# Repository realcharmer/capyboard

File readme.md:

# Capyboard

This repository contains the KiCad source files for the Capyboard development board and its individual modules.

See more at <https://docs.capyboard.dev/modules/mainboard/>.

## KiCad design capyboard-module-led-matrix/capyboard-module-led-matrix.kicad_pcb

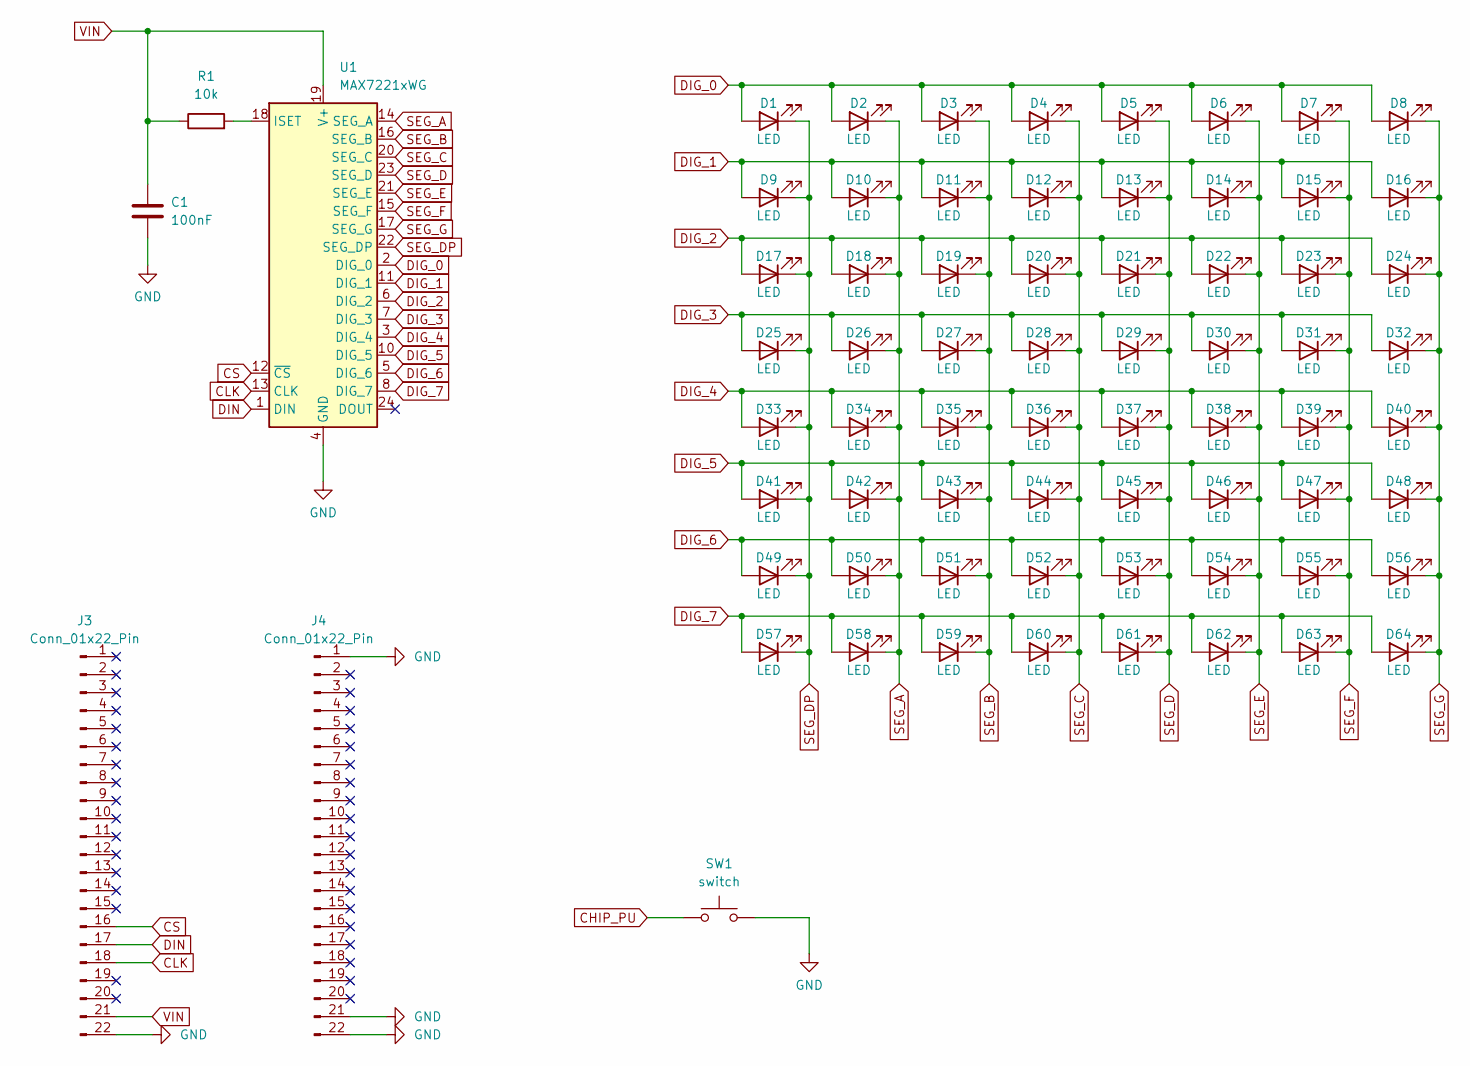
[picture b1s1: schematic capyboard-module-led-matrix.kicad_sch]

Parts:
C1: 100nF; C_0805_2012Metric
D1, D2, D3, D4, D5, D6, D7, D8, D9, D10, D11, D12, D13, D14, D15, D16, D17, D18, D19, D20, D21, D22, D23, D24, D25, D26, D27, D28, D29, D30, D31, D32, D33, D34, D35, D36, D37, D38, D39, D40, D41, D42, D43, D44, D45, D46, D47, D48, D49, D50, D51, D52, D53, D54, D55, D56, D57, D58, D59, D60, D61, D62, D63, D64: LED; LED_0805_2012Metric
J3: Conn_01x22_Pin; PinSocket_1x22_P2.54mm_Vertical_SMD_Pin1Left
J4: Conn_01x22_Pin; PinSocket_1x22_P2.54mm_Vertical_SMD_Pin1Right
R1: 10k; R_0805_2012Metric
SW1: switch; SW_Push_1P1T_NO_CK_KMR2
U1: MAX7221xWG; SOIC-24W_7.5x15.4mm_P1.27mm

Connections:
CHIP_PU: J4.3, SW1.1
CLK: J3.18, U1.13 (CLK)
CS: J3.16, U1.12 (~CS)
DIG_0: D1.2 (A), D2.2 (A), D3.2 (A), D4.2 (A), D5.2 (A), D6.2 (A), D7.2 (A), D8.2 (A), U1.2 (DIG_0)
DIG_1: D9.2 (A), D10.2 (A), D11.2 (A), D12.2 (A), D13.2 (A), D14.2 (A), D15.2 (A), D16.2 (A), U1.11 (DIG_1)
DIG_2: D17.2 (A), D18.2 (A), D19.2 (A), D20.2 (A), D21.2 (A), D22.2 (A), D23.2 (A), D24.2 (A), U1.6 (DIG_2)
DIG_3: D25.2 (A), D26.2 (A), D27.2 (A), D28.2 (A), D29.2 (A), D30.2 (A), D31.2 (A), D32.2 (A), U1.7 (DIG_3)
DIG_4: D33.2 (A), D34.2 (A), D35.2 (A), D36.2 (A), D37.2 (A), D38.2 (A), D39.2 (A), D40.2 (A), U1.3 (DIG_4)
DIG_5: D41.2 (A), D42.2 (A), D43.2 (A), D44.2 (A), D45.2 (A), D46.2 (A), D47.2 (A), D48.2 (A), U1.10 (DIG_5)
DIG_6: D49.2 (A), D50.2 (A), D51.2 (A), D52.2 (A), D53.2 (A), D54.2 (A), D55.2 (A), D56.2 (A), U1.5 (DIG_6)
DIG_7: D57.2 (A), D58.2 (A), D59.2 (A), D60.2 (A), D61.2 (A), D62.2 (A), D63.2 (A), D64.2 (A), U1.8 (DIG_7)
DIN: J3.17, U1.1 (DIN)
unnamed: R1.2, U1.18 (ISET)
SEG_A: D2.1 (K), D10.1 (K), D18.1 (K), D26.1 (K), D34.1 (K), D42.1 (K), D50.1 (K), D58.1 (K), U1.14 (SEG_A)
SEG_B: D3.1 (K), D11.1 (K), D19.1 (K), D27.1 (K), D35.1 (K), D43.1 (K), D51.1 (K), D59.1 (K), U1.16 (SEG_B)
SEG_C: D4.1 (K), D12.1 (K), D20.1 (K), D28.1 (K), D36.1 (K), D44.1 (K), D52.1 (K), D60.1 (K), U1.20 (SEG_C)
SEG_D: D5.1 (K), D13.1 (K), D21.1 (K), D29.1 (K), D37.1 (K), D45.1 (K), D53.1 (K), D61.1 (K), U1.23 (SEG_D)
SEG_DP: D1.1 (K), D9.1 (K), D17.1 (K), D25.1 (K), D33.1 (K), D41.1 (K), D49.1 (K), D57.1 (K), U1.22 (SEG_DP)
SEG_E: D6.1 (K), D14.1 (K), D22.1 (K), D30.1 (K), D38.1 (K), D46.1 (K), D54.1 (K), D62.1 (K), U1.21 (SEG_E)
SEG_F: D7.1 (K), D15.1 (K), D23.1 (K), D31.1 (K), D39.1 (K), D47.1 (K), D55.1 (K), D63.1 (K), U1.15 (SEG_F)
SEG_G: D8.1 (K), D16.1 (K), D24.1 (K), D32.1 (K), D40.1 (K), D48.1 (K), D56.1 (K), D64.1 (K), U1.17 (SEG_G)

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
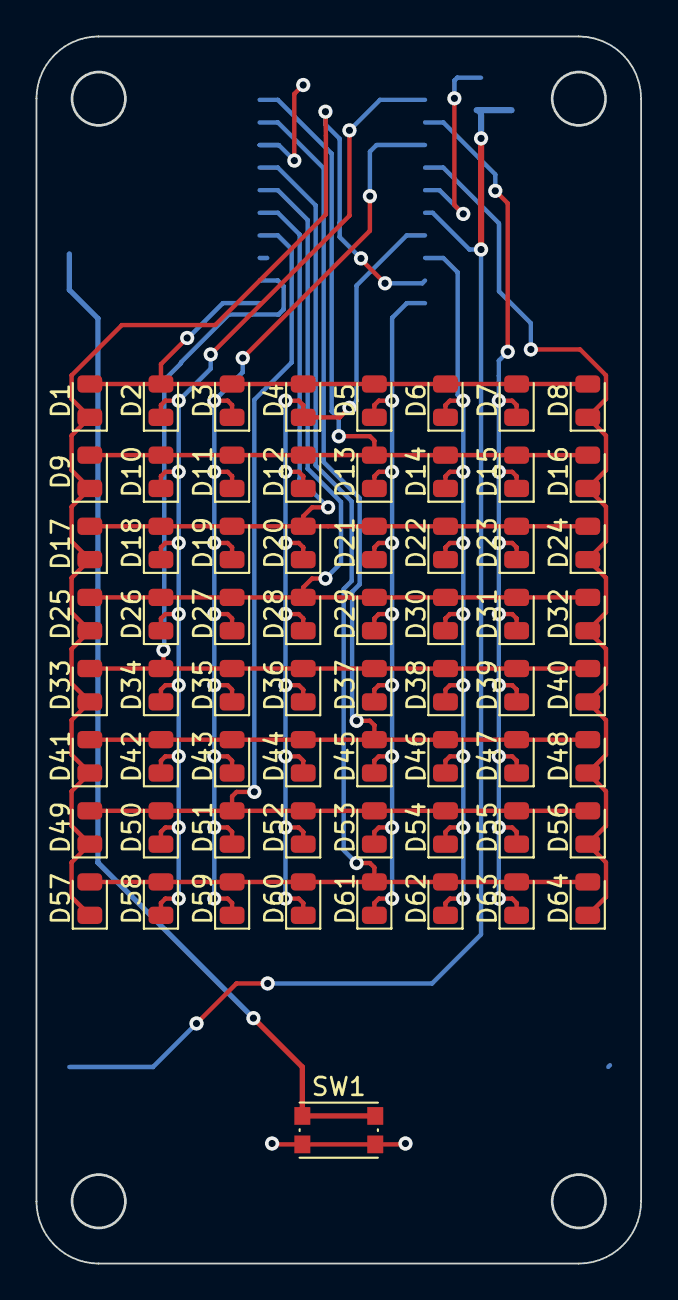
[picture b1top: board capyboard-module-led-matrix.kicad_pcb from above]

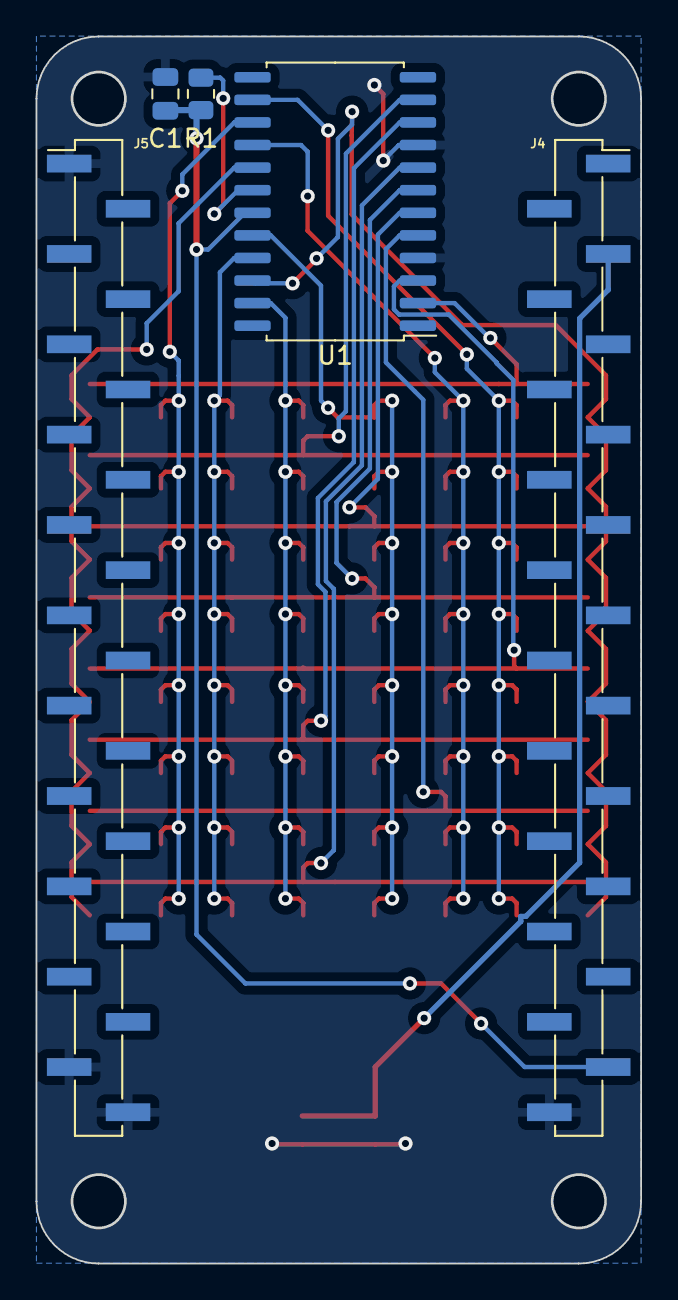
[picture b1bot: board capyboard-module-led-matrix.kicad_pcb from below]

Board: 2 copper layers, 34.0 x 68.9 mm, 70 parts (5 on the bottom side), 20 nets.

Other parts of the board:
J5: Conn_01x22_Pin; PinHeader_1x22_P2.54mm_Vertical_SMD_Pin1Left

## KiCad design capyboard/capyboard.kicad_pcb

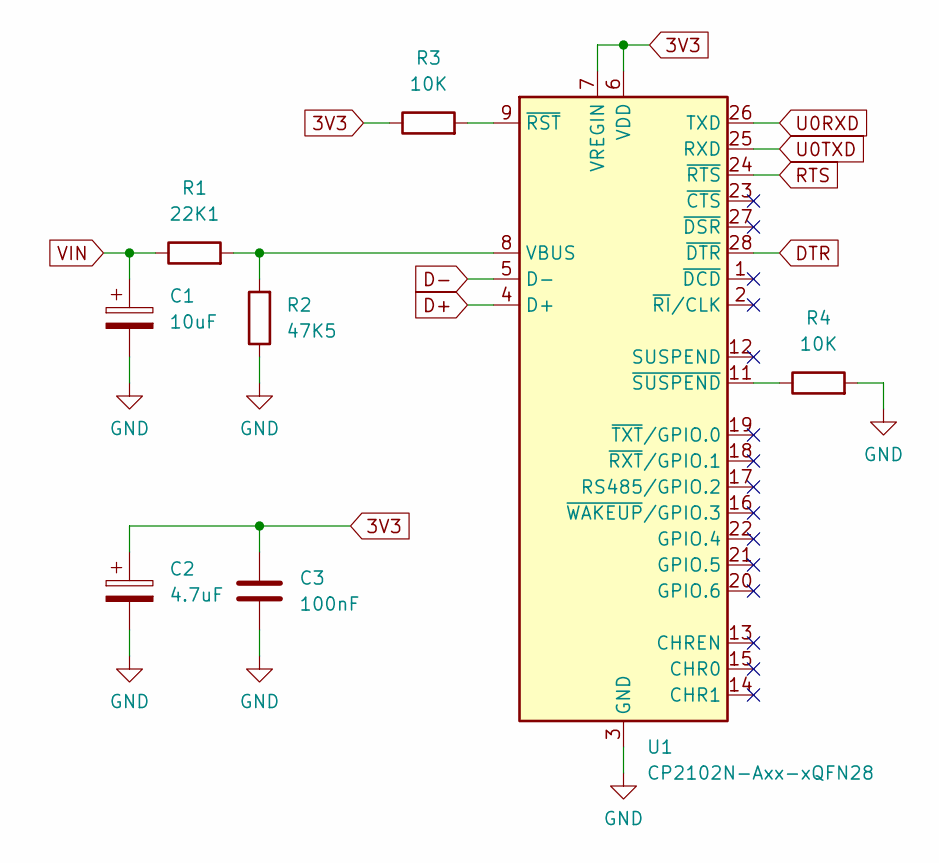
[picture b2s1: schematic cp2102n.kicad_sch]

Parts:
C1: 10uF; C_0805_2012Metric
C2: 4.7uF; C_0805_2012Metric
C3: 100nF; C_0805_2012Metric
R1: 22K1; R_0805_2012Metric
R2: 47K5; R_0805_2012Metric
R3, R4: 10K; R_0805_2012Metric
U1: CP2102N-Axx-xQFN28; QFN-28-1EP_5x5mm_P0.5mm_EP3.35x3.35mm

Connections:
3V3: C2.1, C3.1, R3.1, U1.6 (VDD), U1.7 (VREGIN); also elsewhere on the board
D+: U1.4 (D+); also elsewhere on the board
D-: U1.5 (D-); also elsewhere on the board
DTR: U1.28 (~DTR); also elsewhere on the board
GND: C1.2, C2.2, C3.2, R2.1, R4.2, U1.3 (GND), U1.29 (GND); also elsewhere on the board
unnamed: R1.2, R2.2, U1.8 (VBUS)
unnamed: R3.2, U1.9 (~RST)
unnamed: R4.1, U1.11 (~SUSPEND)
RTS: U1.24 (~RTS); also elsewhere on the board
U0RXD: U1.26 (TXD); also elsewhere on the board
U0TXD: U1.25 (RXD); also elsewhere on the board
VIN: C1.1, R1.1; also elsewhere on the board

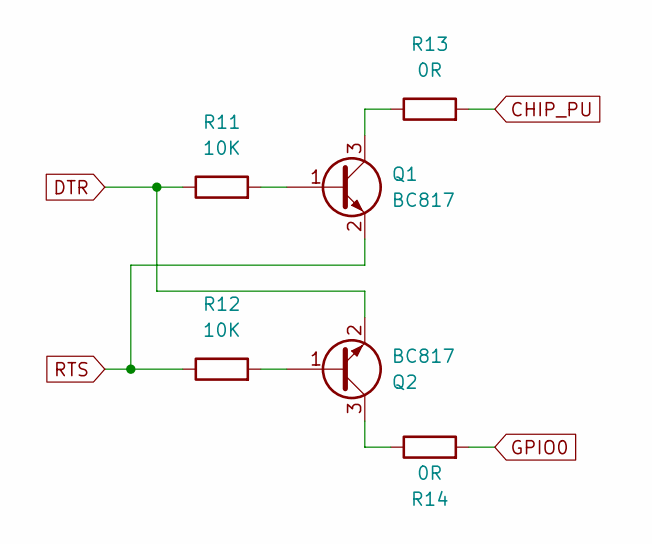
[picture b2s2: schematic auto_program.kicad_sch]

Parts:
Q1, Q2: BC817; SOT-23
R11, R12: 10K; R_0805_2012Metric
R13, R14: 0R; R_0805_2012Metric

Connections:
CHIP_PU: R13.2; also elsewhere on the board
DTR: Q2.2 (E), R11.1; also elsewhere on the board
GPIO0: R14.2; also elsewhere on the board
unnamed: Q1.1 (B), R11.2
unnamed: Q1.3 (C), R13.1
unnamed: Q2.1 (B), R12.2
unnamed: Q2.3 (C), R14.1
RTS: Q1.2 (E), R12.1; also elsewhere on the board

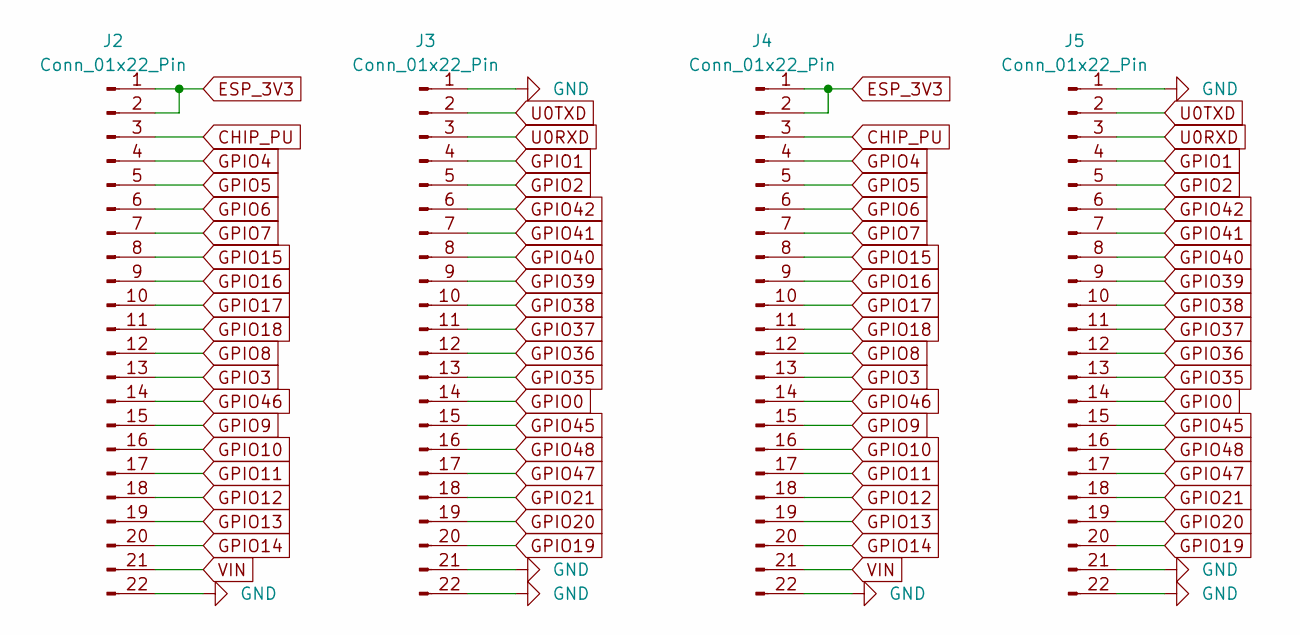
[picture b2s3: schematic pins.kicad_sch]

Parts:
J2: Conn_01x22_Pin; PinSocket_1x22_P2.54mm_Vertical_SMD_Pin1Left
J3: Conn_01x22_Pin; PinSocket_1x22_P2.54mm_Vertical_SMD_Pin1Right
J4: Conn_01x22_Pin; PinHeader_1x22_P2.54mm_Vertical_SMD_Pin1Right
J5: Conn_01x22_Pin; PinHeader_1x22_P2.54mm_Vertical_SMD_Pin1Left

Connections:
CHIP_PU: J2.3, J4.3; also elsewhere on the board
ESP_3V3: J2.1, J2.2, J4.1, J4.2; also elsewhere on the board
GND: J2.22, J3.1, J3.21, J3.22, J4.22, J5.1, J5.21, J5.22; also elsewhere on the board
GPIO0: J3.14, J5.14; also elsewhere on the board
GPIO1: J3.4, J5.4; also elsewhere on the board
GPIO2: J3.5, J5.5; also elsewhere on the board
GPIO3: J2.13, J4.13; also elsewhere on the board
GPIO4: J2.4, J4.4; also elsewhere on the board
GPIO5: J2.5, J4.5; also elsewhere on the board
GPIO6: J2.6, J4.6; also elsewhere on the board
GPIO7: J2.7, J4.7; also elsewhere on the board
GPIO8: J2.12, J4.12; also elsewhere on the board
GPIO9: J2.15, J4.15; also elsewhere on the board
GPIO10: J2.16, J4.16; also elsewhere on the board
GPIO11: J2.17, J4.17; also elsewhere on the board
GPIO12: J2.18, J4.18; also elsewhere on the board
GPIO13: J2.19, J4.19; also elsewhere on the board
GPIO14: J2.20, J4.20; also elsewhere on the board
GPIO15: J2.8, J4.8; also elsewhere on the board
GPIO16: J2.9, J4.9; also elsewhere on the board
GPIO17: J2.10, J4.10; also elsewhere on the board
GPIO18: J2.11, J4.11; also elsewhere on the board
GPIO19: J3.20, J5.20; also elsewhere on the board
GPIO20: J3.19, J5.19; also elsewhere on the board
GPIO21: J3.18, J5.18; also elsewhere on the board
GPIO35: J3.13, J5.13; also elsewhere on the board
GPIO36: J3.12, J5.12; also elsewhere on the board
GPIO37: J3.11, J5.11; also elsewhere on the board
GPIO38: J3.10, J5.10; also elsewhere on the board
GPIO39: J3.9, J5.9; also elsewhere on the board
GPIO40: J3.8, J5.8; also elsewhere on the board
GPIO41: J3.7, J5.7; also elsewhere on the board
GPIO42: J3.6, J5.6; also elsewhere on the board
GPIO45: J3.15, J5.15; also elsewhere on the board
GPIO46: J2.14, J4.14; also elsewhere on the board
GPIO47: J3.17, J5.17; also elsewhere on the board
GPIO48: J3.16, J5.16; also elsewhere on the board
U0RXD: J3.3, J5.3; also elsewhere on the board
U0TXD: J3.2, J5.2; also elsewhere on the board
VIN: J2.21, J4.21; also elsewhere on the board

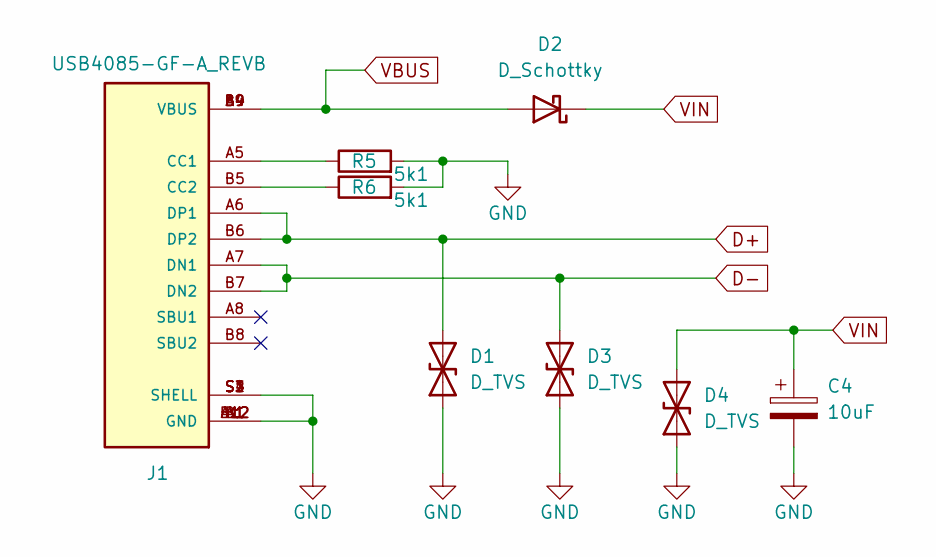
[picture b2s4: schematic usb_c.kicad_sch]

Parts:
C4: 10uF; CP_Elec_5x5.8
D1, D3, D4: D_TVS; D_SOD-323
D2: D_Schottky; D_SOD-123
J1: USB4085-GF-A_REVB; CGT_USB4110; PARTREV B
R5, R6: 5k1; R_0805_2012Metric

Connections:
D+: D1.2 (A2), J1.A6 (DP1), J1.B6 (DP2); also elsewhere on the board
D-: D3.2 (A2), J1.A7 (DN1), J1.B7 (DN2); also elsewhere on the board
GND: C4.2, D1.1 (A1), D3.1 (A1), D4.1 (A1), J1.A1 (GND), J1.A12 (GND), J1.B1 (GND), J1.B12 (GND), J1.S1 (SHELL), J1.S2 (SHELL), J1.S3 (SHELL), J1.S4 (SHELL), R5.2, R6.2; also elsewhere on the board
unnamed: J1.A5 (CC1), R5.1
unnamed: J1.B5 (CC2), R6.1
VBUS: D2.2 (A), J1.A4 (VBUS), J1.A9 (VBUS), J1.B4 (VBUS), J1.B9 (VBUS)
VIN: C4.1, D2.1 (K), D4.2 (A2); also elsewhere on the board

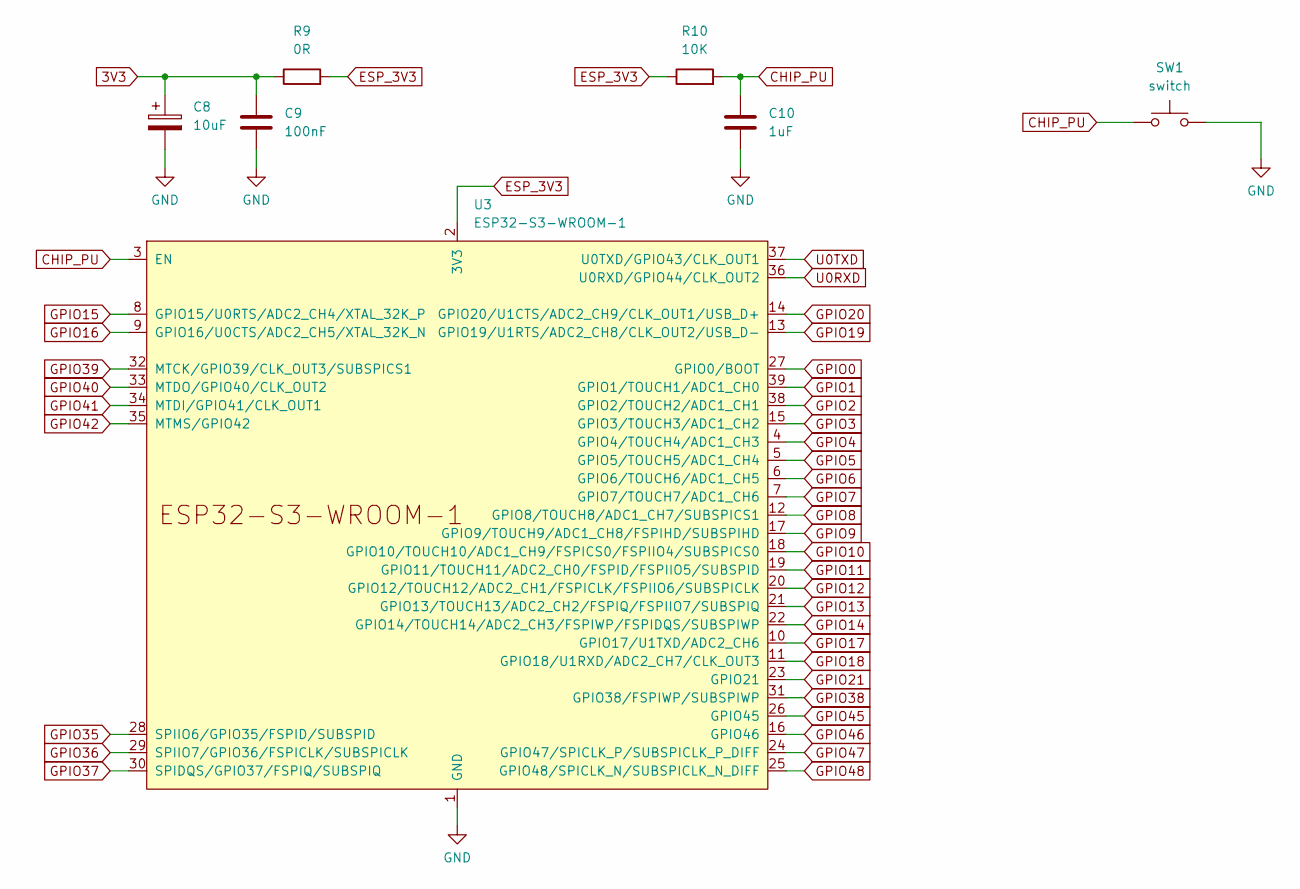
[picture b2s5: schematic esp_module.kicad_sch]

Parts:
C8: 10uF; C_0805_2012Metric
C9: 100nF; C_0805_2012Metric
C10: 1uF; C_0805_2012Metric
R9: 0R; R_0805_2012Metric
R10: 10K; R_0805_2012Metric
SW1: switch; SW_Push_1P1T_NO_CK_KMR2
U3: ESP32-S3-WROOM-1

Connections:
3V3: C8.1, C9.1, R9.1; also elsewhere on the board
CHIP_PU: C10.1, R10.2, SW1.1, U3.3 (EN); also elsewhere on the board
ESP_3V3: R9.2, R10.1, U3.2 (3V3); also elsewhere on the board
GND: C8.2, C9.2, C10.2, SW1.2, U3.1 (GND), U3.40 (GND), U3.41 (GND); also elsewhere on the board
GPIO0: U3.27 (GPIO0/BOOT); also elsewhere on the board
GPIO1: U3.39 (GPIO1/TOUCH1/ADC1_CH0); also elsewhere on the board
GPIO2: U3.38 (GPIO2/TOUCH2/ADC1_CH1); also elsewhere on the board
GPIO3: U3.15 (GPIO3/TOUCH3/ADC1_CH2); also elsewhere on the board
GPIO4: U3.4 (GPIO4/TOUCH4/ADC1_CH3); also elsewhere on the board
GPIO5: U3.5 (GPIO5/TOUCH5/ADC1_CH4); also elsewhere on the board
GPIO6: U3.6 (GPIO6/TOUCH6/ADC1_CH5); also elsewhere on the board
GPIO7: U3.7 (GPIO7/TOUCH7/ADC1_CH6); also elsewhere on the board
GPIO8: U3.12 (GPIO8/TOUCH8/ADC1_CH7/SUBSPICS1); also elsewhere on the board
GPIO9: U3.17 (GPIO9/TOUCH9/ADC1_CH8/FSPIHD/SUBSPIHD); also elsewhere on the board
GPIO10: U3.18 (GPIO10/TOUCH10/ADC1_CH9/FSPICS0/FSPIIO4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); also elsewhere on the board
GPIO11: U3.19 (GPIO11/TOUCH11/ADC2_CH0/FSPID/FSPIIO5/S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); also elsewhere on the board
GPIO12: U3.20 (GPIO12/TOUCH12/ADC2_CH1/FSPICLK/FSPIIO6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); also elsewhere on the board
GPIO13: U3.21 (GPIO13/TOUCH13/ADC2_CH2/FSPIQ/FSPIIO7/S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); also elsewhere on the board
GPIO14: U3.22 (GPIO14/TOUCH14/ADC2_CH3/FSPIWP/FSPIDQS/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); also elsewhere on the board
GPIO15: U3.8 (GPIO15/U0RTS/ADC2_CH4/XTAL_32K_P); also elsewhere on the board
GPIO16: U3.9 (GPIO16/U0CTS/ADC2_CH5/XTAL_32K_N); also elsewhere on the board
GPIO17: U3.10 (GPIO17/U1TXD/ADC2_CH6); also elsewhere on the board
GPIO18: U3.11 (GPIO18/U1RXD/ADC2_CH7/CLK_OUT3); also elsewhere on the board
GPIO19: U3.13 (GPIO19/U1RTS/ADC2_CH8/CLK_OUT2/USB_D-); also elsewhere on the board
GPIO20: U3.14 (GPIO20/U1CTS/ADC2_CH9/CLK_OUT1/USB_D+); also elsewhere on the board
GPIO21: U3.23 (GPIO21); also elsewhere on the board
GPIO35: U3.28 (SPIIO6/GPIO35/FSPID/SUBSPID); also elsewhere on the board
GPIO36: U3.29 (SPIIO7/GPIO36/FSPICLK/SUBSPICLK); also elsewhere on the board
GPIO37: U3.30 (SPIDQS/GPIO37/FSPIQ/SUBSPIQ); also elsewhere on the board
GPIO38: U3.31 (GPIO38/FSPIWP/SUBSPIWP); also elsewhere on the board
GPIO39: U3.32 (MTCK/GPIO39/CLK_OUT3/SUBSPICS1); also elsewhere on the board
GPIO40: U3.33 (MTDO/GPIO40/CLK_OUT2); also elsewhere on the board
GPIO41: U3.34 (MTDI/GPIO41/CLK_OUT1); also elsewhere on the board
GPIO42: U3.35 (MTMS/GPIO42); also elsewhere on the board
GPIO45: U3.26 (GPIO45); also elsewhere on the board
GPIO46: U3.16 (GPIO46); also elsewhere on the board
GPIO47: U3.24 (GPIO47/SPICLK_P/SUBSPICLK_P_DIFF); also elsewhere on the board
GPIO48: U3.25 (GPIO48/SPICLK_N/SUBSPICLK_N_DIFF); also elsewhere on the board
U0RXD: U3.36 (U0RXD/GPIO44/CLK_OUT2); also elsewhere on the board
U0TXD: U3.37 (U0TXD/GPIO43/CLK_OUT1); also elsewhere on the board

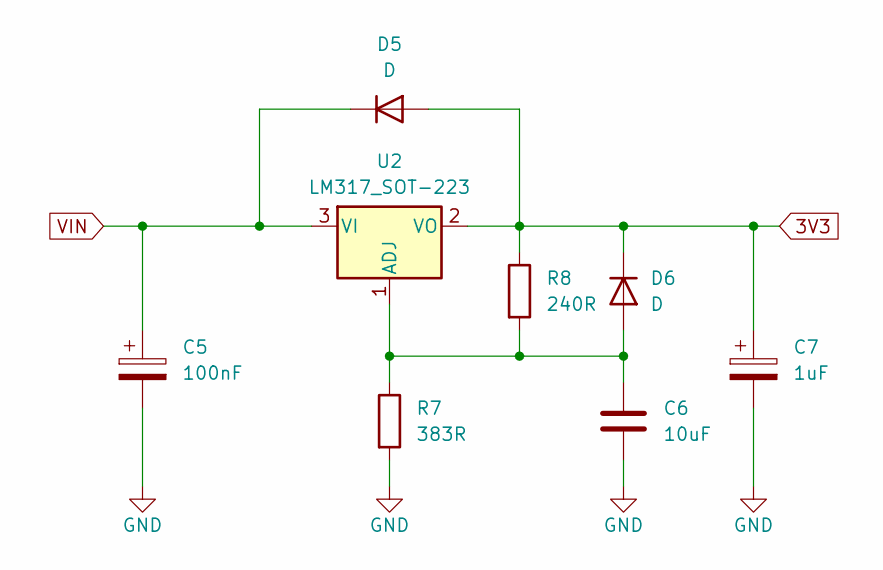
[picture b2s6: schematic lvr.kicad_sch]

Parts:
C5: 100nF; C_0805_2012Metric
C6: 10uF; C_0805_2012Metric
C7: 1uF; C_0805_2012Metric
D5, D6: D; D_SOD-123F
R7: 383R; R_0805_2012Metric
R8: 240R; R_0805_2012Metric
U2: LM317_SOT-223; SOT-223-3_TabPin2

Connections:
3V3: C7.1, D5.2 (A), D6.1 (K), R8.1, U2.2 (VO); also elsewhere on the board
GND: C5.2, C6.2, C7.2, R7.2; also elsewhere on the board
unnamed: C6.1, D6.2 (A), R7.1, R8.2, U2.1 (ADJ)
VIN: C5.1, D5.1 (K), U2.3 (VI); also elsewhere on the board

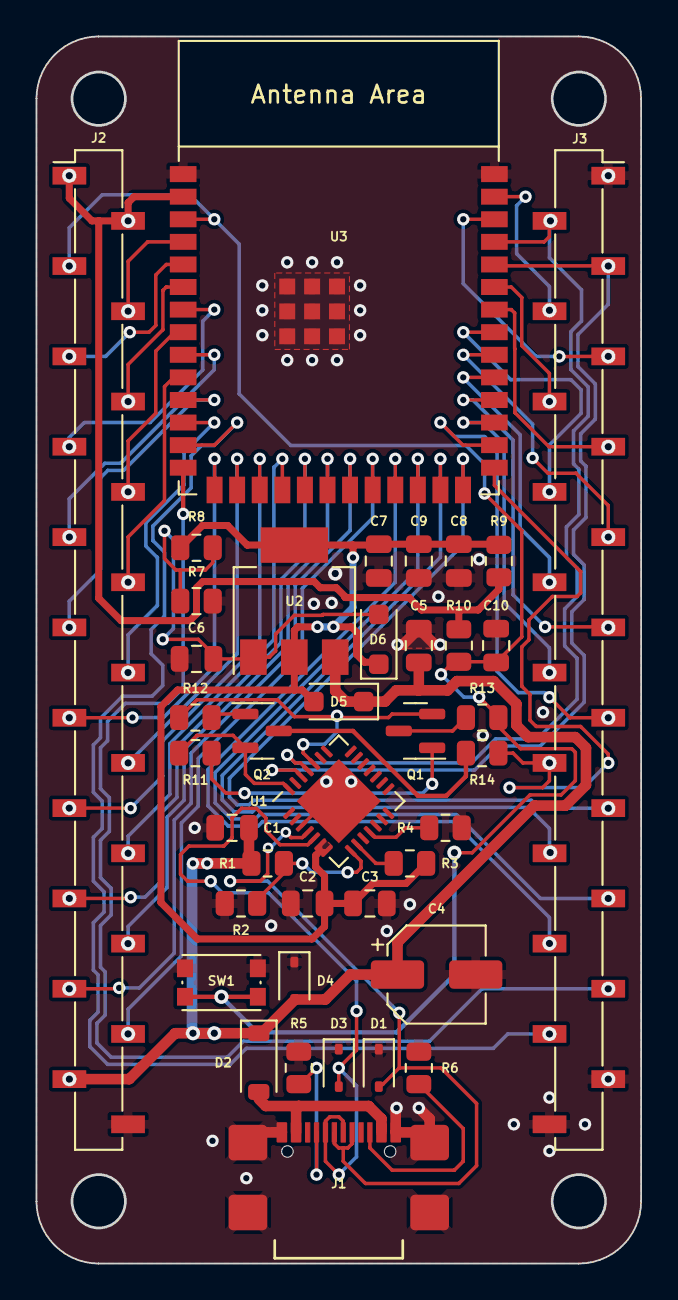
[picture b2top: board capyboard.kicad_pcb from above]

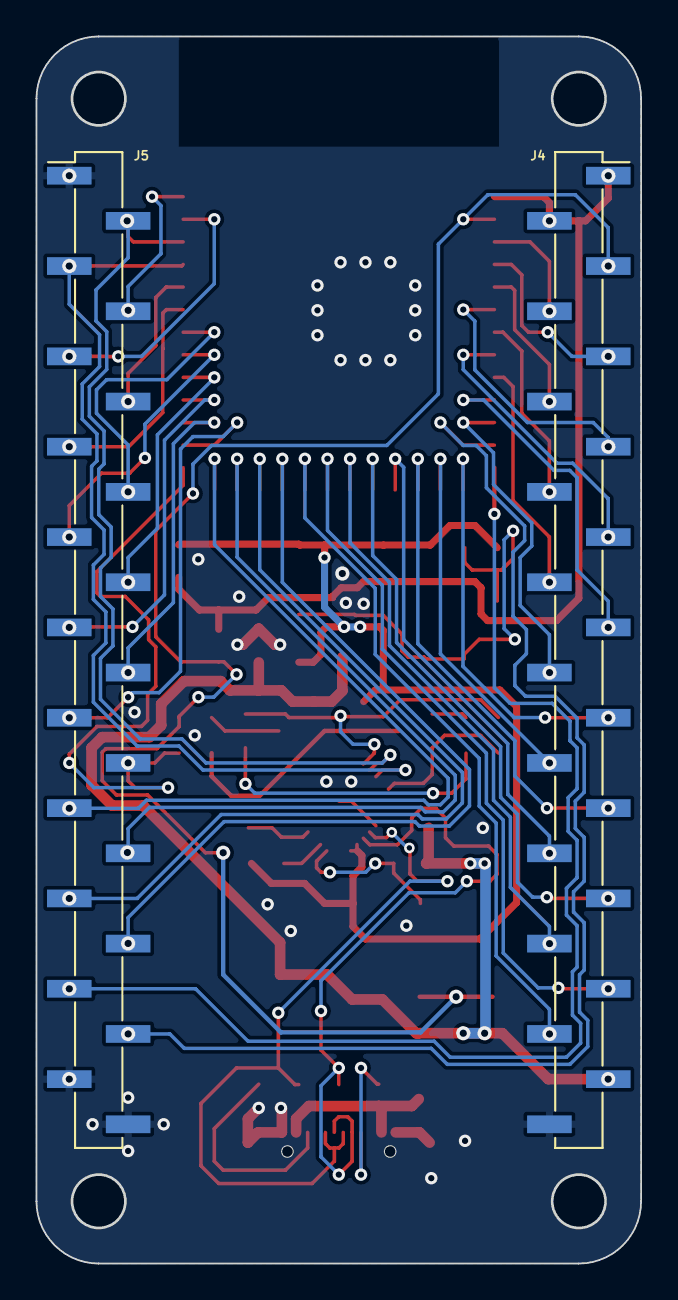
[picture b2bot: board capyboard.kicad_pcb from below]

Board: 2 copper layers, 33.9 x 68.9 mm, 41 parts (2 on the bottom side), 56 nets.

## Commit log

2024-11-20 Add .gitignore
2024-11-20 Add local files
2024-11-20 Move devboard files to separate folder
2024-11-20 Ignore fabrication-toolkit config files
2024-11-20 Add source files for LED matrix module
2024-11-20 Add readme.md
